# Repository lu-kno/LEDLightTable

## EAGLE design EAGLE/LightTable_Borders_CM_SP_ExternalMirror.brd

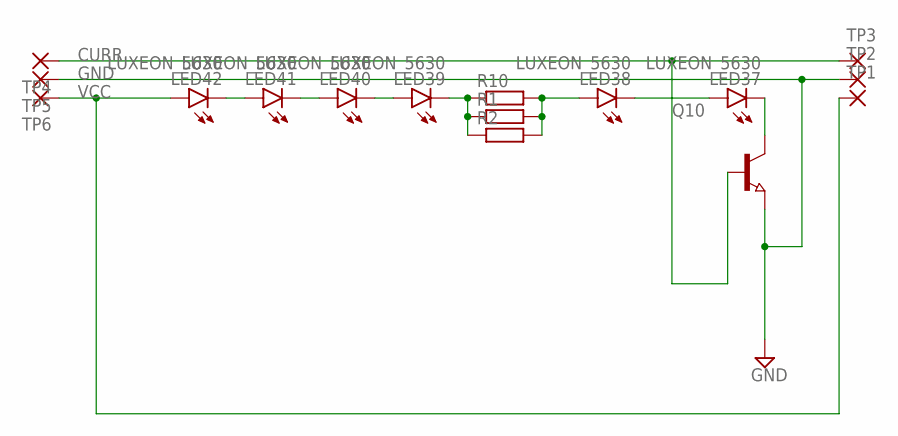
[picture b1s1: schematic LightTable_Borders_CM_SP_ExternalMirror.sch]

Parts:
LED37, LED38, LED39, LED40, LED41, LED42: LUXEON_5630
Q10: NPN-TRANSISTOR_SOT23; SOT23
R1, R2, R10: R-EU_R0805; R0805
TP1, TP2, TP3, TP4, TP5, TP6: LSP10; 1,6/0,8

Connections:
CURR: Q10.1 (B), TP3.1, TP4.1
GND: Q10.2 (E), TP2.1, TP5.1
unnamed: LED39.1@1 (C), LED39.1@2 (C), R1.1, R2.1, R10.1
unnamed: LED38.2 (A), R1.2, R2.2, R10.2
unnamed: LED37.2 (A), LED38.1@1 (C), LED38.1@2 (C)
unnamed: LED37.1@1 (C), LED37.1@2 (C), Q10.3 (C)
unnamed: LED39.2 (A), LED40.1@1 (C), LED40.1@2 (C)
unnamed: LED40.2 (A), LED41.1@1 (C), LED41.1@2 (C)
unnamed: LED41.2 (A), LED42.1@1 (C), LED42.1@2 (C)
VCC: LED42.2 (A), TP1.1, TP6.1

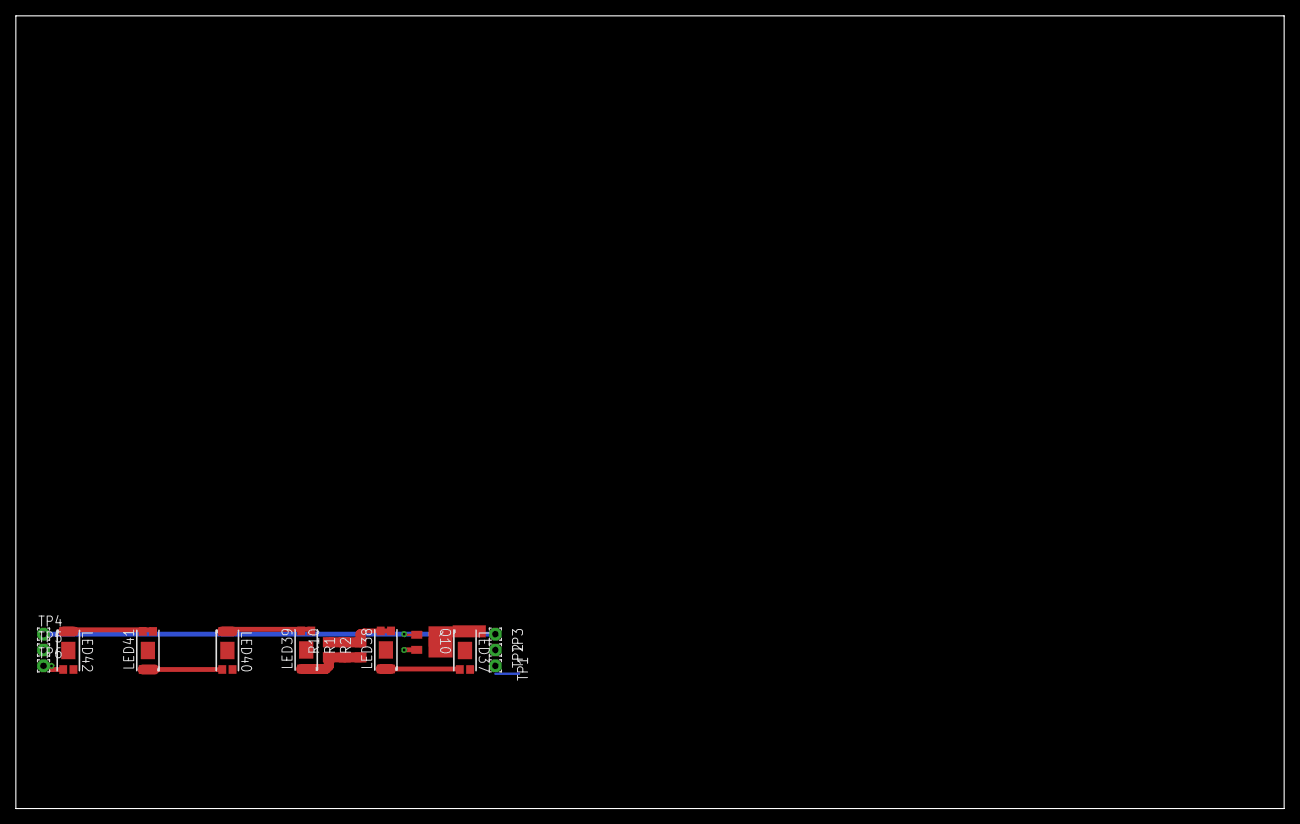
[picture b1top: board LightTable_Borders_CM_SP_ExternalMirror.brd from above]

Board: 2 copper layers, 160.0 x 100.0 mm, 16 parts (0 on the bottom side), 10 nets.

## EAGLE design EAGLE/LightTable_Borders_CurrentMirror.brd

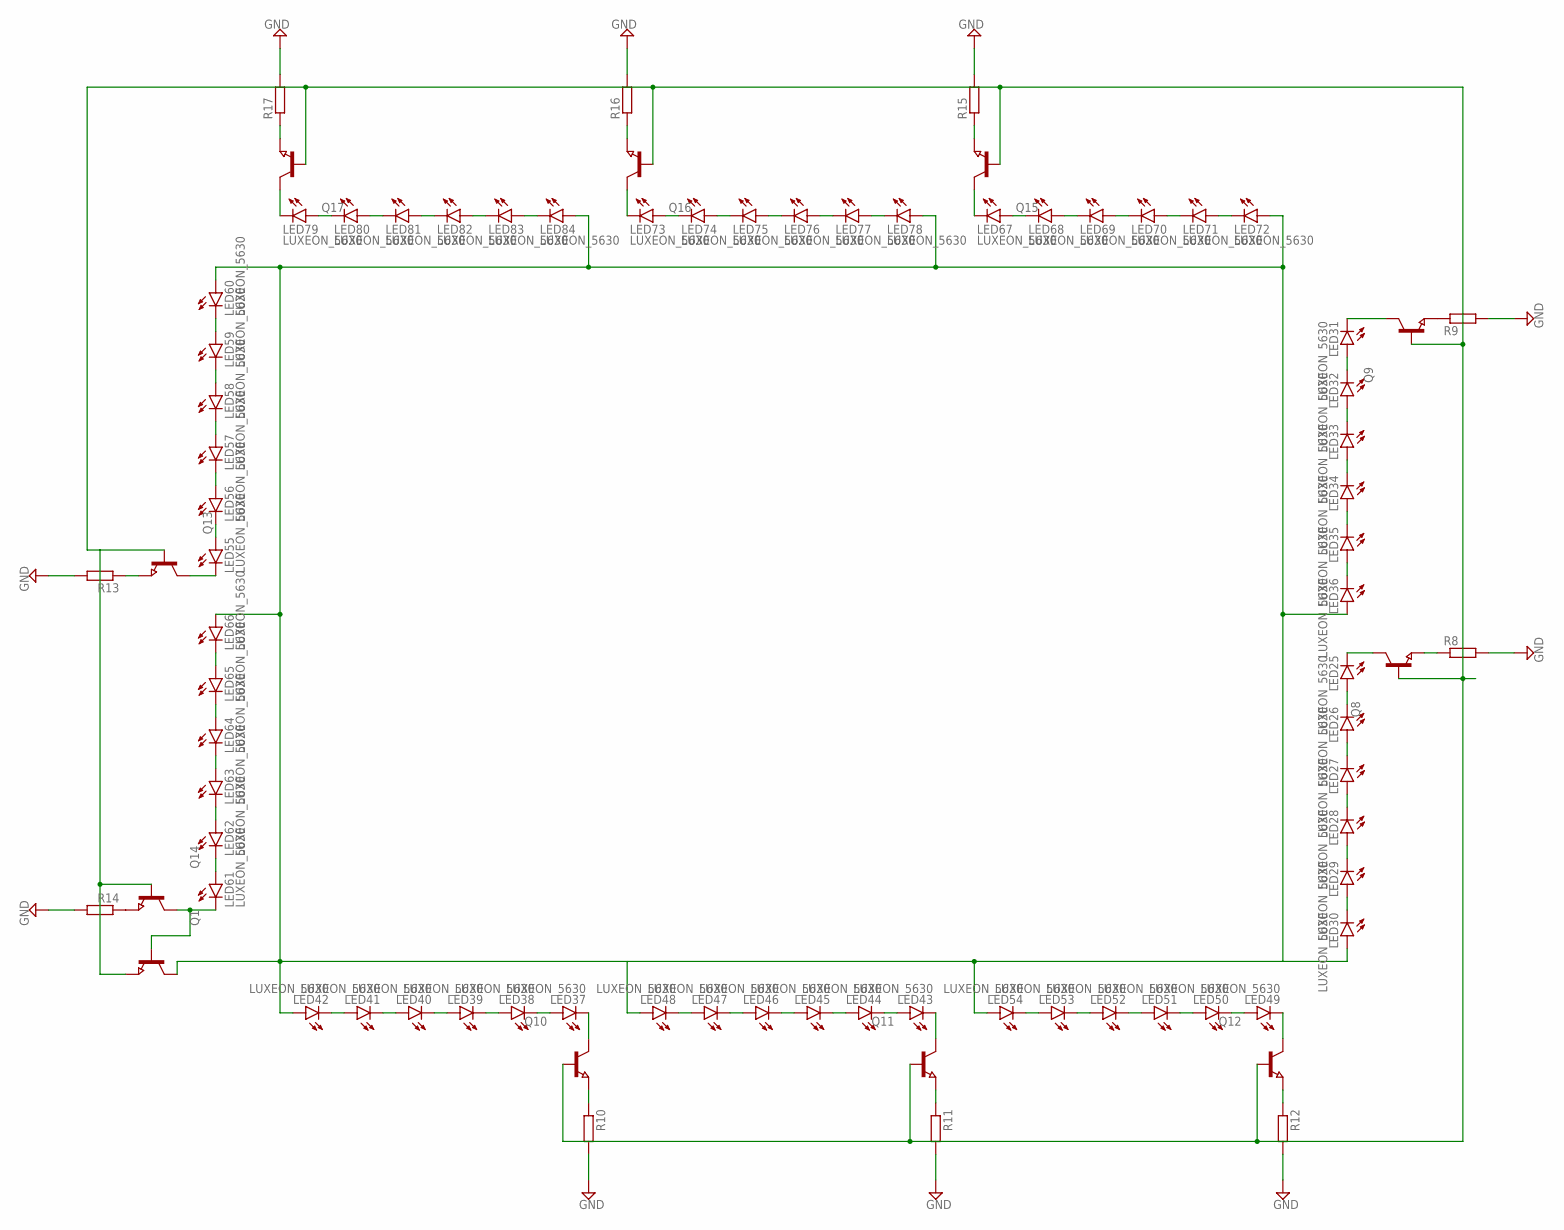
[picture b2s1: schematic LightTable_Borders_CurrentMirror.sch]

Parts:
LED25, LED26, LED27, LED28, LED29, LED30, LED31, LED32, LED33, LED34, LED35, LED36, LED37, LED38, LED39, LED40, LED41, LED42, LED43, LED44, LED45, LED46, LED47, LED48, LED49, LED50, LED51, LED52, LED53, LED54, LED55, LED56, LED57, LED58, LED59, LED60, LED61, LED62, LED63, LED64, LED65, LED66, LED67, LED68, LED69, LED70, LED71, LED72, LED73, LED74, LED75, LED76, LED77, LED78, LED79, LED80, LED81, LED82, LED83, LED84: LUXEON_5630
Q1, Q8, Q9, Q10, Q11, Q12, Q13, Q14, Q15, Q16, Q17: NPN-TRANSISTOR_SOT23; SOT23
R8, R9, R10, R11, R12, R13, R14, R15, R16, R17: R-EU_R0805; R0805

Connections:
GND: R8.2, R9.2, R10.2, R11.2, R12.2, R13.2, R14.2, R15.2, R16.2, R17.2
unnamed: LED25.1@1 (C), LED25.1@2 (C), Q8.3 (C)
unnamed: LED25.2 (A), LED26.1@1 (C), LED26.1@2 (C)
unnamed: LED26.2 (A), LED27.1@1 (C), LED27.1@2 (C)
unnamed: Q8.2 (E), R8.1
unnamed: LED27.2 (A), LED28.1@1 (C), LED28.1@2 (C)
unnamed: LED28.2 (A), LED29.1@1 (C), LED29.1@2 (C)
unnamed: LED29.2 (A), LED30.1@1 (C), LED30.1@2 (C)
unnamed: LED31.1@1 (C), LED31.1@2 (C), Q9.3 (C)
unnamed: LED31.2 (A), LED32.1@1 (C), LED32.1@2 (C)
unnamed: LED32.2 (A), LED33.1@1 (C), LED33.1@2 (C)
unnamed: Q9.2 (E), R9.1
unnamed: LED33.2 (A), LED34.1@1 (C), LED34.1@2 (C)
unnamed: LED34.2 (A), LED35.1@1 (C), LED35.1@2 (C)
unnamed: LED35.2 (A), LED36.1@1 (C), LED36.1@2 (C)
unnamed: LED37.1@1 (C), LED37.1@2 (C), Q10.3 (C)
unnamed: LED37.2 (A), LED38.1@1 (C), LED38.1@2 (C)
unnamed: LED38.2 (A), LED39.1@1 (C), LED39.1@2 (C)
unnamed: Q10.2 (E), R10.1
unnamed: LED39.2 (A), LED40.1@1 (C), LED40.1@2 (C)
unnamed: LED40.2 (A), LED41.1@1 (C), LED41.1@2 (C)
unnamed: LED41.2 (A), LED42.1@1 (C), LED42.1@2 (C)
unnamed: LED43.1@1 (C), LED43.1@2 (C), Q11.3 (C)
unnamed: LED43.2 (A), LED44.1@1 (C), LED44.1@2 (C)
unnamed: LED44.2 (A), LED45.1@1 (C), LED45.1@2 (C)
unnamed: Q11.2 (E), R11.1
unnamed: LED45.2 (A), LED46.1@1 (C), LED46.1@2 (C)
unnamed: LED46.2 (A), LED47.1@1 (C), LED47.1@2 (C)
unnamed: LED47.2 (A), LED48.1@1 (C), LED48.1@2 (C)
unnamed: LED49.1@1 (C), LED49.1@2 (C), Q12.3 (C)
unnamed: LED49.2 (A), LED50.1@1 (C), LED50.1@2 (C)
unnamed: LED50.2 (A), LED51.1@1 (C), LED51.1@2 (C)
unnamed: Q12.2 (E), R12.1
unnamed: LED51.2 (A), LED52.1@1 (C), LED52.1@2 (C)
unnamed: LED52.2 (A), LED53.1@1 (C), LED53.1@2 (C)
unnamed: LED53.2 (A), LED54.1@1 (C), LED54.1@2 (C)
unnamed: LED55.1@1 (C), LED55.1@2 (C), Q13.3 (C)
unnamed: LED55.2 (A), LED56.1@1 (C), LED56.1@2 (C)
unnamed: LED56.2 (A), LED57.1@1 (C), LED57.1@2 (C)
unnamed: Q13.2 (E), R13.1
unnamed: LED57.2 (A), LED58.1@1 (C), LED58.1@2 (C)
unnamed: LED58.2 (A), LED59.1@1 (C), LED59.1@2 (C)
unnamed: LED59.2 (A), LED60.1@1 (C), LED60.1@2 (C)
unnamed: Q1.2 (E), Q8.1 (B), Q9.1 (B), Q10.1 (B), Q11.1 (B), Q12.1 (B), Q13.1 (B), Q14.1 (B), Q15.1 (B), Q16.1 (B), Q17.1 (B)
unnamed: LED61.1@1 (C), LED61.1@2 (C), Q1.1 (B), Q14.3 (C)
unnamed: LED61.2 (A), LED62.1@1 (C), LED62.1@2 (C)
unnamed: LED62.2 (A), LED63.1@1 (C), LED63.1@2 (C)
unnamed: Q14.2 (E), R14.1
unnamed: LED63.2 (A), LED64.1@1 (C), LED64.1@2 (C)
unnamed: LED64.2 (A), LED65.1@1 (C), LED65.1@2 (C)
unnamed: LED65.2 (A), LED66.1@1 (C), LED66.1@2 (C)
unnamed: LED67.1@1 (C), LED67.1@2 (C), Q15.3 (C)
unnamed: LED67.2 (A), LED68.1@1 (C), LED68.1@2 (C)
unnamed: LED68.2 (A), LED69.1@1 (C), LED69.1@2 (C)
unnamed: Q15.2 (E), R15.1
unnamed: LED69.2 (A), LED70.1@1 (C), LED70.1@2 (C)
unnamed: LED70.2 (A), LED71.1@1 (C), LED71.1@2 (C)
unnamed: LED71.2 (A), LED72.1@1 (C), LED72.1@2 (C)
unnamed: LED73.1@1 (C), LED73.1@2 (C), Q16.3 (C)
unnamed: LED73.2 (A), LED74.1@1 (C), LED74.1@2 (C)
unnamed: LED74.2 (A), LED75.1@1 (C), LED75.1@2 (C)
unnamed: Q16.2 (E), R16.1
unnamed: LED75.2 (A), LED76.1@1 (C), LED76.1@2 (C)
unnamed: LED76.2 (A), LED77.1@1 (C), LED77.1@2 (C)
unnamed: LED77.2 (A), LED78.1@1 (C), LED78.1@2 (C)
unnamed: LED79.1@1 (C), LED79.1@2 (C), Q17.3 (C)
unnamed: LED79.2 (A), LED80.1@1 (C), LED80.1@2 (C)
unnamed: LED80.2 (A), LED81.1@1 (C), LED81.1@2 (C)
unnamed: Q17.2 (E), R17.1
unnamed: LED81.2 (A), LED82.1@1 (C), LED82.1@2 (C)
unnamed: LED82.2 (A), LED83.1@1 (C), LED83.1@2 (C)
unnamed: LED83.2 (A), LED84.1@1 (C), LED84.1@2 (C)
unnamed: LED30.2 (A), LED36.2 (A), LED42.2 (A), LED48.2 (A), LED54.2 (A), LED60.2 (A), LED66.2 (A), LED72.2 (A), LED78.2 (A), LED84.2 (A), Q1.3 (C)

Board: 2 copper layers, 81 parts (0 on the bottom side), 73 nets, no tracks yet.

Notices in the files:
parts and their libraries:
led: Lumileds 5630 Datasheet DS201 20130228 ©2013 Philips Lumileds Lighting Company.
